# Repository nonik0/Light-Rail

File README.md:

# Light Rail

## Overview & Acknowledgements

Light Rail is a minimalist, interactive PCB game that simulates trains traveling along tracks, picking up and delivering cargo from platforms. The track is composed of yellow LEDs arranged in lines, which illuminate sequentially to create the effect of trains moving along the tracks. Next to each of the eight forks and crosses in the track is a button to switch its state. The board also has a three-character seven-segment display for showing the game status and/or score and four more buttons underneath the track for gameplay control. Light Rail can be powered with two LIR2032 batteries or via USB.

I also want to acknowledge and thank [PCBWay](https://www.pcbway.com/) for their generous support of this project! Even before I had the initial idea, PCBWay had already reached out to me asking if I would like to collaborate on my next project. However, I didn't actually see the email until I started looking into how I wanted to manufacture prototypes for Light Rail. Just getting the email and seeing that others were liking my older projects gave me a big motivation boost to continue with this project, be creative, and make something of my own. Overall, my experience with PCBWay was great and I would definitely recommend checking them out for your own projects!

For more details about my design goals, process, and ordering and production experience with PCBWay, please see my full [project writeup](https://altonimb.us/light-rail/)!

### Work Left
- first working game prototype
- further game ideas and testing
- investigate CR2032 batteries in series

## Hardware
The hardware is designed in KiCad 8.0 and all design files are included in the [hardware/kicad8.0](hardware/kicad8.0) directory.

The main hardware components are:
- [ATMega32u4](https://www.microchip.com/en-us/product/atmega32u4) 8-bit MCU
- [IS31FL3731](https://www.lumissil.com/applications/industrial/appliance/major-appliances/range-hood/is31fl3731) matrix LED driver (charliplexing)
- [AS1115](https://ams-osram.com/products/drivers/led-drivers/ams-as1115-led-driver-ic) seven-segment LED display driver
- [KCSC02-105](https://www.kingbright.com/attachments/file/psearch/000/00/00/KCSC02-105(Ver.12A).pdf) seven-segment LED display
- [MIC5219](https://ww1.microchip.com/downloads/en/DeviceDoc/MIC5219-500mA-Peak-Output-LDO-Regulator-DS20006021A.pdf) 3.3V LDS Regulator
- Yellow "track" and red "platform" LEDs, 144 total

See the [Bill of Material (BoM)](hardware/documents/Light_Rail_BOM.xlsx) for complete list of components used and my [project writeup](WRITEUP.md) for more details.

## Firmware

The firmware initially started as a C++/PlatformIO project, which can be found in the [firmware/cpp](firmware/cpp) directory. Before I actually received the inital prototype boards I decided to pivot and write everything in Rust, which can be found in the [firmware/rust](firmware/rust) directory. As part of the effort to get back to where I left off with the C++ firmware, I did the following:
- Wrote a new [AS1115 driver](https://github.com/nonik0/as1115)
- Wrote new tone library for avr-hal (TODO: integrate into avr-hal and open PR)
- Updated existing fork of [IS31FL3731](https://github.com/nonik0/is31fl3731) driver to latest embedded-hal with other minor additions

TODO: basic overview of game design and firmware components (in second writeup?)

## Images

#### Prototype

#### Schematic

#### PCB Layout

#### Render

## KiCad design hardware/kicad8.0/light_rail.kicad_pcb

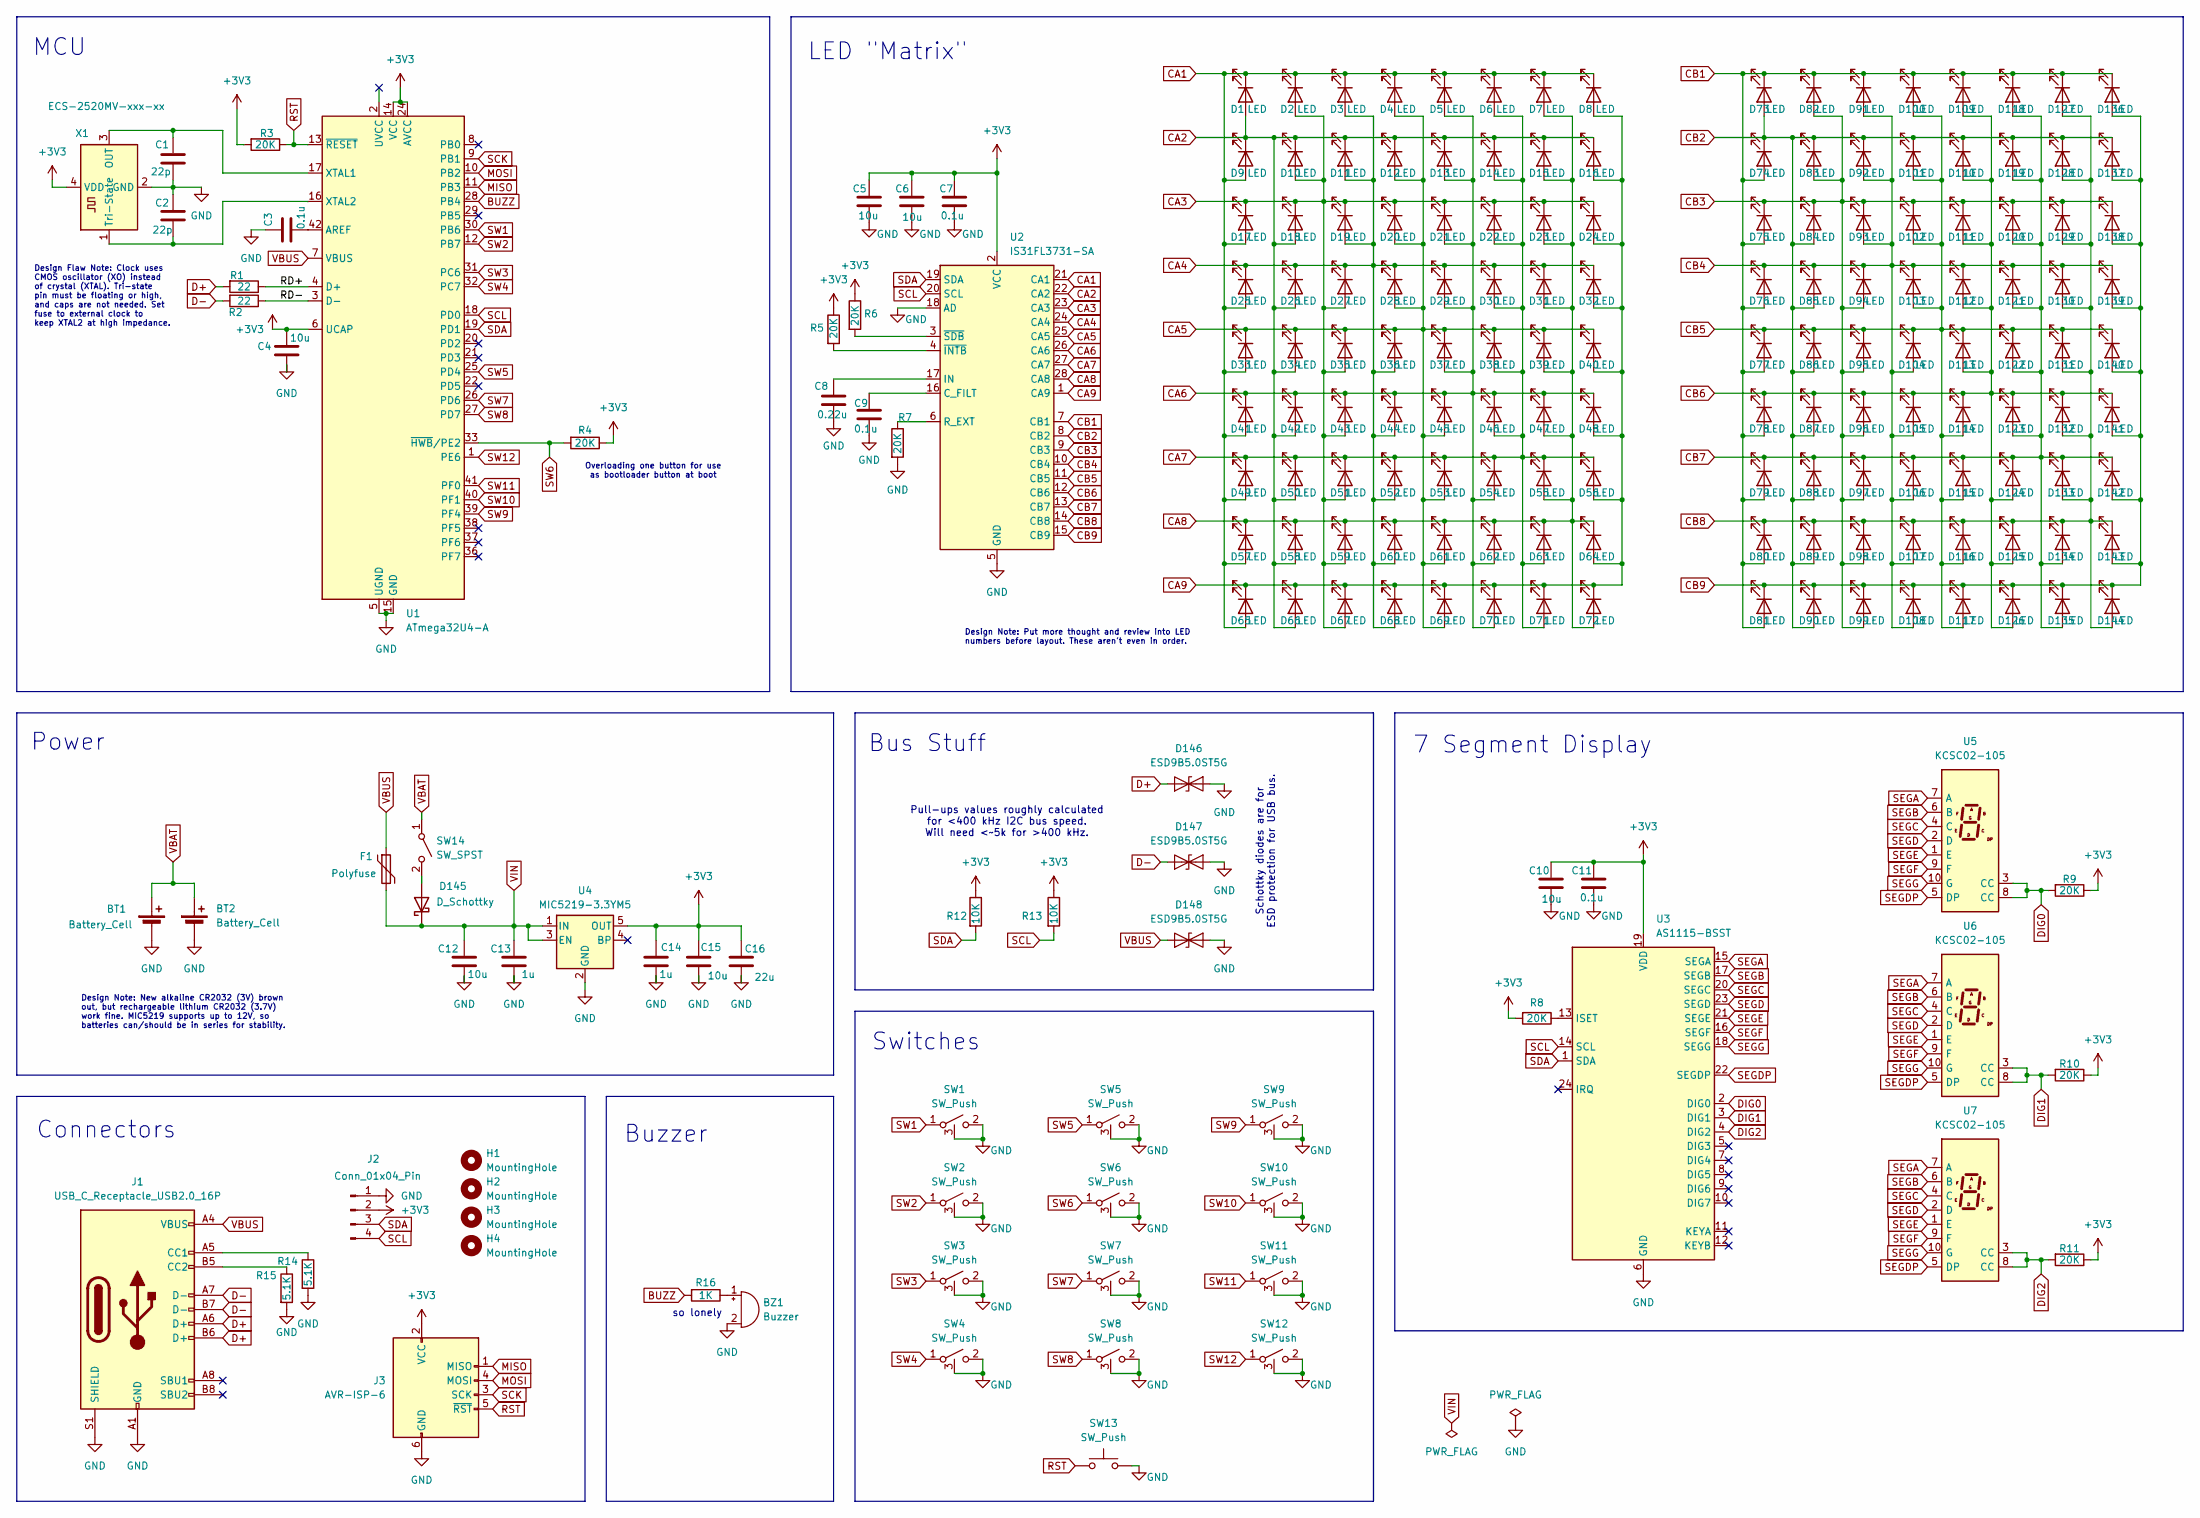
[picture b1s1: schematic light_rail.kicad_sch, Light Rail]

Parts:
BT1, BT2: Battery_Cell; BatteryHolder_Keystone_3034_1x20mm
BZ1: Buzzer; Buzzer_Murata_PKLCS1212E
C1, C2: 22p; C_0805_2012Metric
C3, C7, C9, C11: 0.1u; C_0805_2012Metric
C4, C5, C6, C10, C12, C15: 10u; C_0805_2012Metric
C8: 0.22u; C_0805_2012Metric
C13, C14: 1u; C_0805_2012Metric
C16: 22u; C_0805_2012Metric
D1, D9, D10, D16, D17, D18, D19, D21, D23, D27, D28, D32, D39, D41, D43, D48, D49, D50, D53, D54, D57, D59, D60, D61, D63, D64, D66, D68, D69, D70, D76, D85, D86, D88, D96, D97, D100, D101, D103, D105, D106, D108, D114, D117, D118, D121, D122, D123, D124, D125, D128, D132, D135, D137, D139, D140, D141, D143: LED; LED_0805_TrainTrack
D2, D6, D7, D12, D14, D20, D26, D33, D34, D36, D47, D58, D62, D71, D75, D78, D89, D92, D94, D104, D110, D111, D112, D115, D116, D134, D136: LED; LED_0805_NoSilkscreen
D3, D11, D38, D46, D67: LED; LED_0805_TrainTrackBendStart3
D4, D35, D72, D90, D91, D99, D102, D109, D127, D142: LED; LED_0805_TrainTrackBendStart4
D5, D13, D15, D22, D25, D37, D42, D44, D45, D79, D82, D83, D84, D120, D133, D138, D144: LED; LED_0805_TrainTrackBend1
D8, D30, D52, D56, D65, D74, D77, D98, D129, D130: LED; LED_0805_TrainTrackBend2
D24, D40, D51, D55, D73, D93, D126, D131: LED; LED_0805_TrainTrackEmpty
D29: LED; LED_0805_TrainTrackInnerBend2
D31, D80, D87: LED; LED_0805_TrainTrackBendStart2
D81, D95, D107, D119: LED; LED_0805_TrainTrackBendStart1
D113: LED; LED_0805_TrainTrackInnerBend1
D145: D_Schottky; D_0805_2012Metric
D146, D147, D148: ESD9B5.0ST5G; D_0402_1005Metric
F1: Polyfuse; D_0603_1608Metric
H1, H2, H3, H4: MountingHole; MountingHole_Custom
J1: USB_C_Receptacle_USB2.0_16P; USB_C_Receptacle_HCTL_HC-TYPE-C-16P-01A
J2: Conn_01x04_Pin; PinHeader_1x04_P2.54mm_Vertical
J3: AVR-ISP-6; PinHeader_2x03_P2.54mm_Vertical
R1, R2: 22; R_0805_2012Metric
R3, R4, R5, R6, R7, R8, R9, R10, R11: 20K; R_0805_2012Metric
R12, R13: 10K; R_0805_2012Metric
R14, R15: 5.1K; R_0603_1608Metric
R16: 1K; R_0805_2012Metric
SW1, SW2, SW3, SW4, SW5, SW6, SW7, SW8, SW9, SW10, SW11, SW12: SW_Push; SW_SPST_PTS526_JLeadsWGndPin
SW13: SW_Push; SW_Push_SPST_NO_Alps_SKRK
SW14: SW_SPST; SW_SPDT_PCM12
U1: ATmega32U4-A; TQFP-44_10x10mm_P0.8mm
U2: IS31FL3731-SA; SSOP-28_5.3x10.2mm_P0.65mm
U3: AS1115-BSST; QSOP-24_3.9x8.7mm_P0.635mm
U4: MIC5219-3.3YM5; SOT-23-5
U5, U6, U7: KCSC02-105
X1: ECS-2520MV-xxx-xx; Oscillator_SMD_ECS_2520MV-xxx-xx-4Pin_2.5x2.0mm

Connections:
+3V3: C4.1, C5.1, C6.1, C7.1, C10.1, C11.1, C14.1, C15.1, C16.1, J2.2, J3.2 (VCC), R3.2, R4.1, R5.1, R6.1, R8.2, R9.1, R10.1, R11.1, R12.1, R13.1, U1.6 (UCAP), U1.14 (VCC), U1.24 (AVCC), U1.34 (VCC), U1.44 (AVCC), U2.2 (VCC), U3.19 (VDD), U4.5 (OUT), X1.4 (VDD)
/RD+: R1.1, U1.4 (D+)
/RD-: R2.1, U1.3 (D-)
BUZZ: R16.2, U1.28 (PB4)
CA1: D1.1 (K), D2.1 (K), D3.1 (K), D4.1 (K), D5.1 (K), D6.1 (K), D7.1 (K), D8.1 (K), D9.2 (A), D17.2 (A), D25.2 (A), D33.2 (A), D41.2 (A), D49.2 (A), D57.2 (A), D65.2 (A), U2.21 (CA1)
CA2: D1.2 (A), D9.1 (K), D10.1 (K), D11.1 (K), D12.1 (K), D13.1 (K), D14.1 (K), D15.1 (K), D16.1 (K), D18.2 (A), D26.2 (A), D34.2 (A), D42.2 (A), D50.2 (A), D58.2 (A), D66.2 (A), U2.22 (CA2)
CA3: D2.2 (A), D10.2 (A), D17.1 (K), D18.1 (K), D19.1 (K), D20.1 (K), D21.1 (K), D22.1 (K), D23.1 (K), D24.1 (K), D27.2 (A), D35.2 (A), D43.2 (A), D51.2 (A), D59.2 (A), D67.2 (A), U2.23 (CA3)
CA4: D3.2 (A), D11.2 (A), D19.2 (A), D25.1 (K), D26.1 (K), D27.1 (K), D28.1 (K), D29.1 (K), D30.1 (K), D31.1 (K), D32.1 (K), D36.2 (A), D44.2 (A), D52.2 (A), D60.2 (A), D68.2 (A), U2.24 (CA4)
CA5: D4.2 (A), D12.2 (A), D20.2 (A), D28.2 (A), D33.1 (K), D34.1 (K), D35.1 (K), D36.1 (K), D37.1 (K), D38.1 (K), D39.1 (K), D40.1 (K), D45.2 (A), D53.2 (A), D61.2 (A), D69.2 (A), U2.25 (CA5)
CA6: D5.2 (A), D13.2 (A), D21.2 (A), D29.2 (A), D37.2 (A), D41.1 (K), D42.1 (K), D43.1 (K), D44.1 (K), D45.1 (K), D46.1 (K), D47.1 (K), D48.1 (K), D54.2 (A), D62.2 (A), D70.2 (A), U2.26 (CA6)
CA7: D6.2 (A), D14.2 (A), D22.2 (A), D30.2 (A), D38.2 (A), D46.2 (A), D49.1 (K), D50.1 (K), D51.1 (K), D52.1 (K), D53.1 (K), D54.1 (K), D55.1 (K), D56.1 (K), D63.2 (A), D71.2 (A), U2.27 (CA7)
CA8: D7.2 (A), D15.2 (A), D23.2 (A), D31.2 (A), D39.2 (A), D47.2 (A), D55.2 (A), D57.1 (K), D58.1 (K), D59.1 (K), D60.1 (K), D61.1 (K), D62.1 (K), D63.1 (K), D64.1 (K), D72.2 (A), U2.28 (CA8)
CA9: D8.2 (A), D16.2 (A), D24.2 (A), D32.2 (A), D40.2 (A), D48.2 (A), D56.2 (A), D64.2 (A), D65.1 (K), D66.1 (K), D67.1 (K), D68.1 (K), D69.1 (K), D70.1 (K), D71.1 (K), D72.1 (K), U2.1 (CA9)
CB1: D73.1 (K), D74.2 (A), D75.2 (A), D76.2 (A), D77.2 (A), D78.2 (A), D79.2 (A), D80.2 (A), D81.2 (A), D82.1 (K), D91.1 (K), D100.1 (K), D109.1 (K), D118.1 (K), D127.1 (K), D136.1 (K), U2.7 (CB1)
CB2: D73.2 (A), D74.1 (K), D83.1 (K), D84.2 (A), D85.2 (A), D86.2 (A), D87.2 (A), D88.2 (A), D89.2 (A), D90.2 (A), D92.1 (K), D101.1 (K), D110.1 (K), D119.1 (K), D128.1 (K), D137.1 (K), U2.8 (CB2)
CB3: D75.1 (K), D82.2 (A), D83.2 (A), D84.1 (K), D93.1 (K), D94.2 (A), D95.2 (A), D96.2 (A), D97.2 (A), D98.2 (A), D99.2 (A), D102.1 (K), D111.1 (K), D120.1 (K), D129.1 (K), D138.1 (K), U2.9 (CB3)
CB4: D76.1 (K), D85.1 (K), D91.2 (A), D92.2 (A), D93.2 (A), D94.1 (K), D103.1 (K), D104.2 (A), D105.2 (A), D106.2 (A), D107.2 (A), D108.2 (A), D112.1 (K), D121.1 (K), D130.1 (K), D139.1 (K), U2.10 (CB4)
CB5: D77.1 (K), D86.1 (K), D95.1 (K), D100.2 (A), D101.2 (A), D102.2 (A), D103.2 (A), D104.1 (K), D113.1 (K), D114.2 (A), D115.2 (A), D116.2 (A), D117.2 (A), D122.1 (K), D131.1 (K), D140.1 (K), U2.11 (CB5)
CB6: D78.1 (K), D87.1 (K), D96.1 (K), D105.1 (K), D109.2 (A), D110.2 (A), D111.2 (A), D112.2 (A), D113.2 (A), D114.1 (K), D123.1 (K), D124.2 (A), D125.2 (A), D126.2 (A), D132.1 (K), D141.1 (K), U2.12 (CB6)
CB7: D79.1 (K), D88.1 (K), D97.1 (K), D106.1 (K), D115.1 (K), D118.2 (A), D119.2 (A), D120.2 (A), D121.2 (A), D122.2 (A), D123.2 (A), D124.1 (K), D133.1 (K), D134.2 (A), D135.2 (A), D142.1 (K), U2.13 (CB7)
CB8: D80.1 (K), D89.1 (K), D98.1 (K), D107.1 (K), D116.1 (K), D125.1 (K), D127.2 (A), D128.2 (A), D129.2 (A), D130.2 (A), D131.2 (A), D132.2 (A), D133.2 (A), D134.1 (K), D143.1 (K), D144.2 (A), U2.14 (CB8)
CB9: D81.1 (K), D90.1 (K), D99.1 (K), D108.1 (K), D117.1 (K), D126.1 (K), D135.1 (K), D136.2 (A), D137.2 (A), D138.2 (A), D139.2 (A), D140.2 (A), D141.2 (A), D142.2 (A), D143.2 (A), D144.1 (K), U2.15 (CB9)
D+: D146.1 (A1), J1.A6 (D+), J1.B6 (D+), R1.2
D-: D147.1 (A1), J1.A7 (D-), J1.B7 (D-), R2.2
DIG0: R9.2, U3.2 (DIG0), U5.3 (CC), U5.8 (CC)
DIG1: R10.2, U3.3 (DIG1), U6.3 (CC), U6.8 (CC)
DIG2: R11.2, U3.4 (DIG2), U7.3 (CC), U7.8 (CC)
GND: BT1.2 (-), BT2.2 (-), BZ1.2 (-), C1.2, C2.1, C3.1, C4.2, C5.2, C6.2, C7.2, C8.2, C9.2, C10.2, C11.2, C12.2, C13.2, C14.2, C15.2, C16.2, D146.2 (A2), D147.2 (A2), D148.2 (A2), J1.A1 (GND), J1.A12 (GND), J1.B1 (GND), J1.B12 (GND), J1.S1 (SHIELD), J2.1, J3.6 (GND), R7.2, R14.2, R15.2, SW1.2 (B), SW1.3 (GND), SW2.2 (B), SW2.3 (GND), SW3.2 (B), SW3.3 (GND), SW4.2 (B), SW4.3 (GND), SW5.2 (B), SW5.3 (GND), SW6.2 (B), SW6.3 (GND), SW7.2 (B), SW7.3 (GND), SW8.2 (B), SW8.3 (GND), SW9.2 (B), SW9.3 (GND), SW10.2 (B), SW10.3 (GND), SW11.2 (B), SW11.3 (GND), SW12.2 (B), SW12.3 (GND), SW13.2, U1.5 (UGND), U1.15 (GND), U1.23 (GND), U1.35 (GND), U1.43 (GND), U2.5 (GND), U2.18 (AD), U3.6 (GND), U4.2 (GND), X1.2 (GND)
MISO: J3.1 (MISO), U1.11 (PB3)
MOSI: J3.4 (MOSI), U1.10 (PB2)
unnamed: BZ1.1 (+), R16.1
unnamed: D145.2 (A), SW14.2 (B)
unnamed: J1.A5 (CC1), R14.1
unnamed: J1.B5 (CC2), R15.1
unnamed: C3.2, U1.42 (AREF)
unnamed: C1.1, U1.17 (XTAL1), X1.3 (OUT)
unnamed: C2.2, U1.16 (XTAL2), X1.1 (Tri-State)
unnamed: C9.1, U2.16 (C_FILT)
unnamed: C8.1, U2.17 (IN)
unnamed: R7.1, U2.6 (R_EXT)
unnamed: R5.2, U2.4 (~INTB)
unnamed: R6.2, U2.3 (~SDB)
unnamed: R8.1, U3.13 (ISET)
RST: J3.5 (~RST), R3.1, SW13.1, U1.13 (~RESET)
SCK: J3.3 (SCK), U1.9 (PB1)
SCL: J2.4, R13.2, U1.18 (PD0), U2.20 (SCL), U3.14 (SCL)
SDA: J2.3, R12.2, U1.19 (PD1), U2.19 (SDA), U3.1 (SDA)
SEGA: U3.15 (SEGA), U5.7 (A), U6.7 (A), U7.7 (A)
SEGB: U3.17 (SEGB), U5.6 (B), U6.6 (B), U7.6 (B)
SEGC: U3.20 (SEGC), U5.4 (C), U6.4 (C), U7.4 (C)
SEGD: U3.23 (SEGD), U5.2 (D), U6.2 (D), U7.2 (D)
SEGDP: U3.22 (SEGDP), U5.5 (DP), U6.5 (DP), U7.5 (DP)
SEGE: U3.21 (SEGE), U5.1 (E), U6.1 (E), U7.1 (E)
SEGF: U3.16 (SEGF), U5.9 (F), U6.9 (F), U7.9 (F)
SEGG: U3.18 (SEGG), U5.10 (G), U6.10 (G), U7.10 (G)
SW1: SW1.1 (A), U1.30 (PB6)
SW2: SW2.1 (A), U1.12 (PB7)
SW3: SW3.1 (A), U1.31 (PC6)
SW4: SW4.1 (A), U1.32 (PC7)
SW5: SW5.1 (A), U1.25 (PD4)
SW6: R4.2, SW6.1 (A), U1.33 (~HWB/PE2)
SW7: SW7.1 (A), U1.26 (PD6)
SW8: SW8.1 (A), U1.27 (PD7)
SW9: SW9.1 (A), U1.39 (PF4)
SW10: SW10.1 (A), U1.40 (PF1)
SW11: SW11.1 (A), U1.41 (PF0)
SW12: SW12.1 (A), U1.1 (PE6)
VBAT: BT1.1 (+), BT2.1 (+), SW14.1 (A)
VBUS: D148.1 (A1), F1.1, J1.A4 (VBUS), J1.A9 (VBUS), J1.B4 (VBUS), J1.B9 (VBUS), U1.7 (VBUS)
VIN: C12.1, C13.1, D145.1 (K), F1.2, U4.1 (IN), U4.3 (EN)

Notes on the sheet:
Design Flaw Note: Clock uses CMOS oscillator (XO) instead of crystal (XTAL). Tri-state pin must be floating or high, and caps are not needed. Set fuse to external clock to keep XTAL2 at high impedance.
Design Note: New alkaline CR2032 (3V) brown out, but rechargeable lithium CR2032 (3.7V) work fine. MIC5219 supports up to 12V, so batteries can/should be in series for stability.
Pull-ups values roughly calculated for <400 kHz I2C bus speed. Will need <~5k for >400 kHz.
LED "Matrix"
Design Note: Put more thought and review into LED numbers before layout. These aren't even in order.
Bus Stuff
Power
MCU
Buzzer
Connectors
Switches
so lonely
Overloading one button for use as bootloader button at boot
7 Segment Display
Schottky diodes are for ESD protection for USB bus.

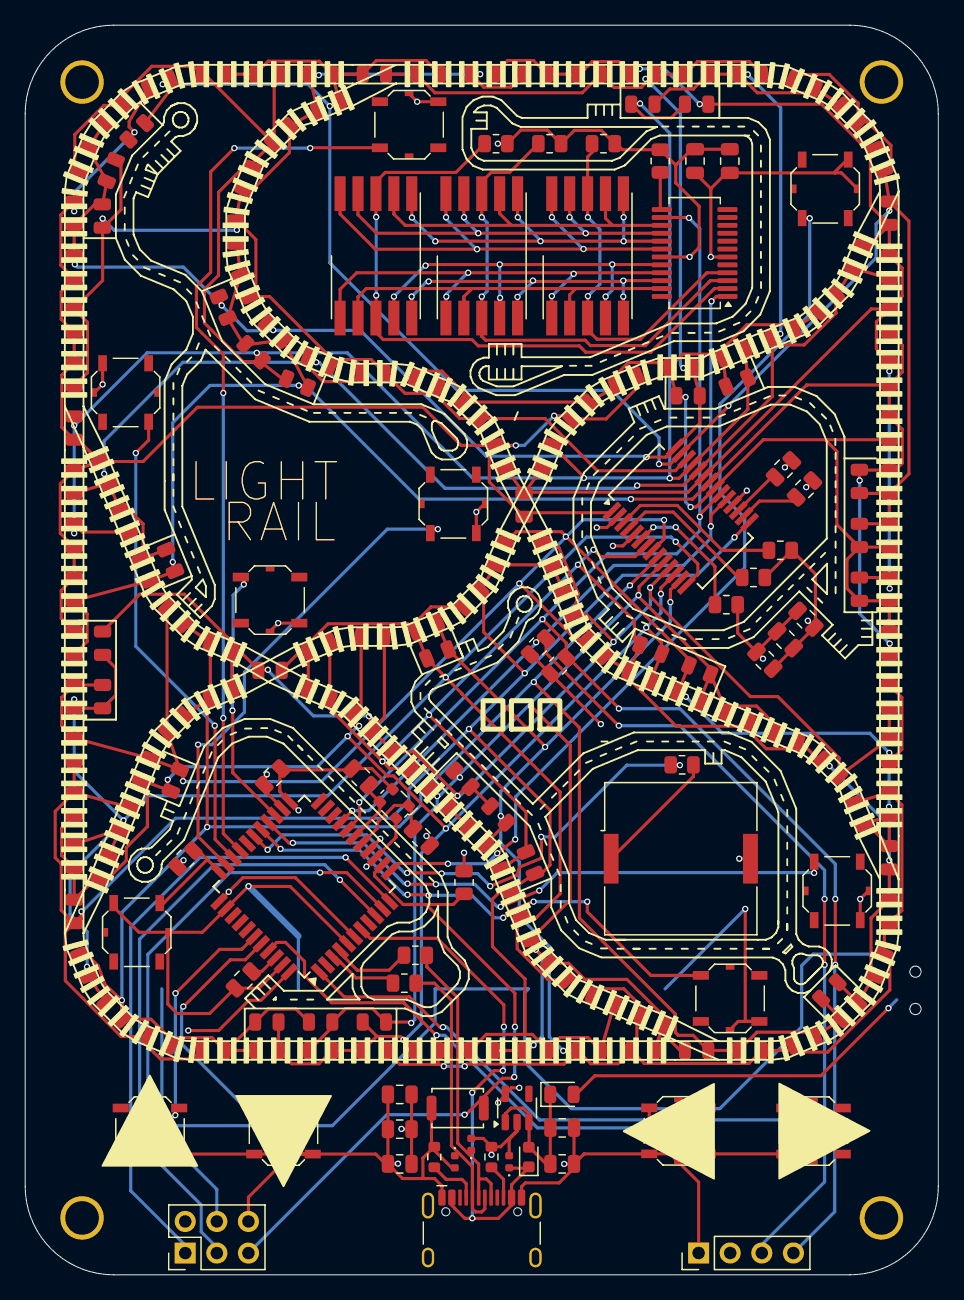
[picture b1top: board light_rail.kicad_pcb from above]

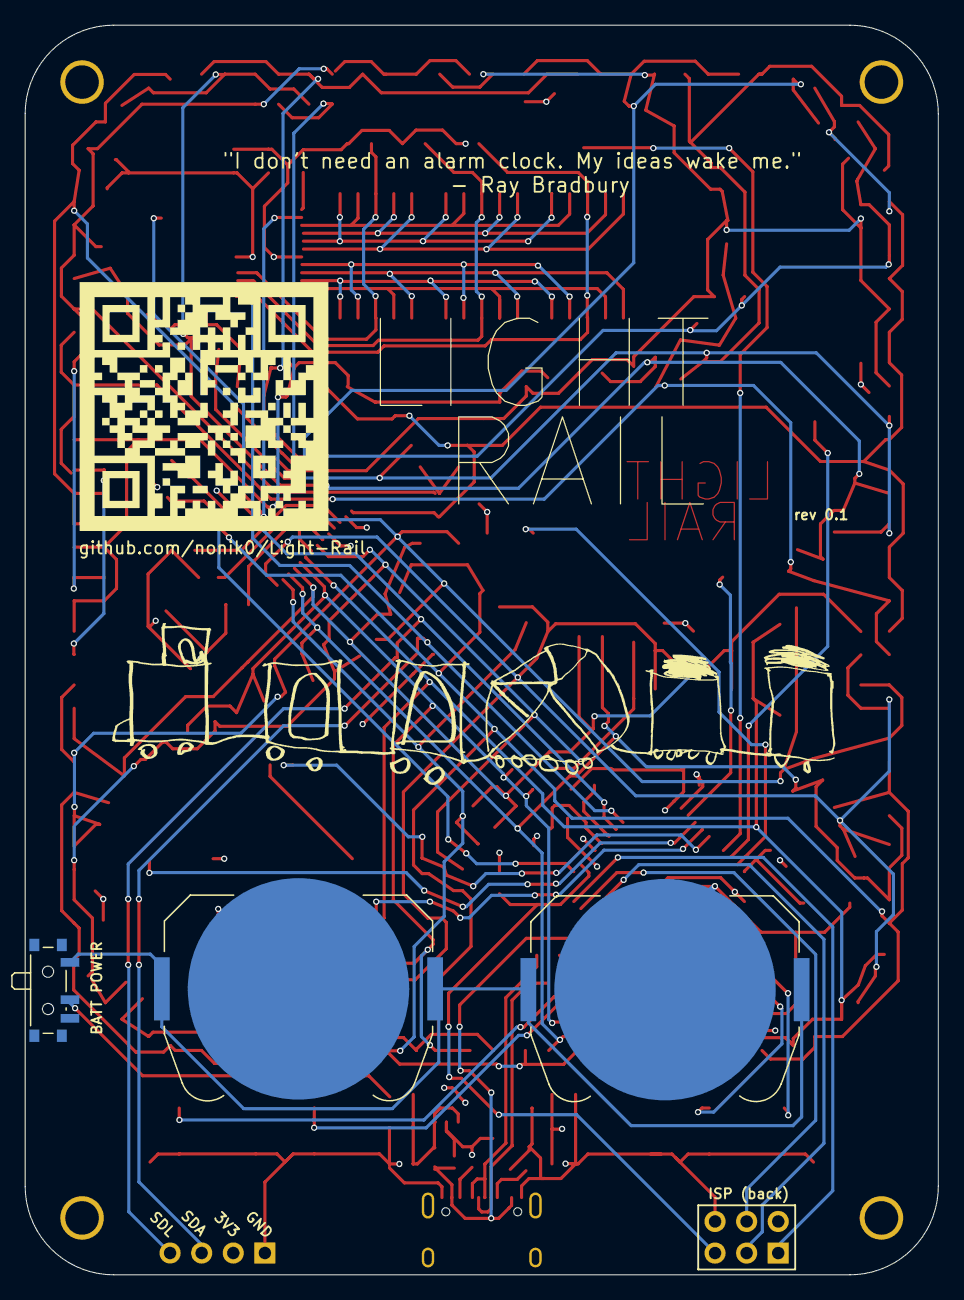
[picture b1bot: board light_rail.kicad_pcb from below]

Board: 4 copper layers, 73.4 x 100.5 mm, 213 parts (3 on the bottom side), 70 nets.

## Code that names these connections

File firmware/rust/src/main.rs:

#![no_std]
#![no_main]
#![feature(abi_avr_interrupt)]
#![feature(const_trait_impl)]
#![feature(panic_info_message)]
#![feature(type_alias_impl_trait)]

// TODO: can print to digits before panic halting
#[cfg(not(feature = "panic_to_digits"))]
#[macro_export]
macro_rules! panic_with_error {
    ($error_code:expr) => {
        panic!()
    };
}

use atmega_hal::adc;
use core::cell::RefCell;
use embedded_hal::delay::DelayNs;
use embedded_hal_bus::i2c::{self};
#[cfg(not(feature = "panic_to_digits"))]
use panic_halt as _;

type Adc = atmega_hal::adc::Adc<CoreClock>;
#[cfg(feature = "atmega32u4")]
type CoreClock = atmega_hal::clock::MHz8;
#[cfg(feature = "atmega328p")]
type CoreClock = atmega_hal::clock::MHz16;
type Delay = atmega_hal::delay::Delay<CoreClock>;
type Eeprom = atmega_hal::eeprom::Eeprom;
type I2c = atmega_hal::i2c::I2c<CoreClock>;

mod cargo;
mod game;
mod game_settings;
mod game_state;
mod input;
mod location;
mod modes;
#[cfg(feature = "panic_to_digits")]
mod panic;
mod platform;
mod random;
mod switch;
#[cfg_attr(not(feature = "atmega32u4"), path = "notone.rs")]
mod tone;
mod train;

const NUM_BUTTONS: usize = 12;
const NUM_DIGITS: u8 = 3;
const DIGITS_I2C_ADDR: u8 = as1115::DEFAULT_ADDRESS;
const LEDS_I2C_ADDR: u8 = is31fl3731::DEFAULT_ADDRESS;

#[avr_device::entry]
fn main() -> ! {
    let dp = atmega_hal::Peripherals::take().unwrap();
    let pins = atmega_hal::pins!(dp);
    let mut delay = Delay::new();
    let i2c = I2c::new(
        dp.TWI,
        #[cfg(feature = "atmega32u4")]
        pins.pd1.into_pull_up_input(),
        #[cfg(feature = "atmega328p")]
        pins.pc4.into_pull_up_input(),
        #[cfg(feature = "atmega32u4")]
        pins.pd0.into_pull_up_input(),
        #[cfg(feature = "atmega328p")]
        pins.pc5.into_pull_up_input(),
        400_000,
    );
    let i2c_ref_cell = RefCell::new(i2c);

    #[cfg(feature = "atmega32u4")]
    let board_buzzer = tone::TimerTone::new(dp.TC3, pins.pb4.into_output().downgrade());
    #[cfg(feature = "atmega328p")]
    let board_buzzer = tone::TimerTone::new();

    let eeprom = Eeprom::new(dp.EEPROM);
    let settings = game_settings::GameSettings::new(eeprom);

    let mut board_digits =
        as1115::AS1115::new_with_addr(i2c::RefCellDevice::new(&i2c_ref_cell), DIGITS_I2C_ADDR);
    board_digits.init(settings.digit_brightness_level()).ok();
    board_digits.clear().ok();

    #[cfg(feature = "atmega32u4")]
    let input_pins = [
        pins.pb6.into_pull_up_input().downgrade(),
        pins.pb7.into_pull_up_input().downgrade(),
        pins.pc6.into_pull_up_input().downgrade(),
        pins.pc7.into_pull_up_input().downgrade(),
        pins.pd4.into_pull_up_input().downgrade(),
        pins.pe2.into_pull_up_input().downgrade(),
        pins.pd6.into_pull_up_input().downgrade(),
        pins.pd7.into_pull_up_input().downgrade(),
        pins.pf4.into_pull_up_input().downgrade(),
        pins.pf1.into_pull_up_input().downgrade(),
        pins.pf0.into_pull_up_input().downgrade(),
        pins.pe6.into_pull_up_input().downgrade(),
    ];
    #[cfg(feature = "atmega328p")]
    let input_pins = [
        pins.pd0.into_pull_up_input().downgrade(),
        pins.pd1.into_pull_up_input().downgrade(),
        pins.pd2.into_pull_up_input().downgrade(),
        pins.pd3.into_pull_up_input().downgrade(),
        pins.pd4.into_pull_up_input().downgrade(),
        pins.pd5.into_pull_up_input().downgrade(),
        pins.pd6.into_pull_up_input().downgrade(),
        pins.pd7.into_pull_up_input().downgrade(),
        pins.pb0.into_pull_up_input().downgrade(),
        pins.pb1.into_pull_up_input().downgrade(),
        pins.pb2.into_pull_up_input().downgrade(),
        pins.pb3.into_pull_up_input().downgrade(),
    ];
    let board_input = input::BoardInput::new(input_pins);

    let mut board_leds =
        is31fl3731::IS31FL3731::new(i2c::RefCellDevice::new(&i2c_ref_cell), LEDS_I2C_ADDR);
    board_leds.setup_blocking(&mut delay).unwrap(); // TODO: why does OK hang???
    board_leds.clear_blocking().ok();

    // generate random seed from ADC temperature sensor
    let mut adc = Adc::new(dp.ADC, Default::default());
    let mut seed: u32 = 0;
    for i in 0..8 {
        // using 4 LSB bits x 8 readings for 32 bit seed
        let reading = adc.read_blocking(&adc::channel::Temperature);
        let lsb = (reading & 0xF) as u32;
        seed |= lsb << (i * 4);
    }
    random::Rand::seed(seed);

    let cars = [train::Car::default(); game_state::MAX_CARS];
    let mut game = game::Game::new(
        board_buzzer,
        board_digits,
        board_input,
        board_leds,
        cars,
        settings,
    );
    game.restart();

    loop {
        game.tick();
        delay.delay_ms(game.base_delay());
    }
}

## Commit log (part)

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2024-11-15 changes for fab
2024-11-20 fab updates 2
2024-11-30 post-prod schematic fix, should be no change
2024-12-14 starting boilerplate
2024-12-14 more boilerplate work
2024-12-14 BoM fix
2024-12-15 basic working prototype
2024-12-15 minor stuff
2025-01-09 testing board
2025-01-09 rust firmware start
2025-01-09 partial progress
2025-01-09 untested full graph, switch tests
2025-01-09 working animation!
2025-01-09 BOM fix for RST switch
2025-01-14 fixes
2025-01-14 working is31 driver in rust
2025-01-15 as1115 driver
2025-01-15 use is31 github driver
2025-01-15 starting to figure out tone
2025-01-16 partial tone impl in rust
2025-01-16 some progress on timer
2025-01-17 rust progress
2025-01-19 minor
2025-01-28 working tone with timer1
2025-01-28 starting game structure
2025-01-29 location refactoring
2025-01-30 misc
2025-01-30 change to timer3
2025-01-31 game logic progress
2025-01-31 more progress, untested
2025-01-31 starting LocationUpdate changes
2025-02-01 location update impl
2025-02-02 progmem refactor in progress
2025-02-02 added design comments to schematic, added schematic image
2025-02-02 adding more images and moving around stuff
2025-02-02 resize images
2025-02-05 nearly there for basic animation demo
2025-02-05 first working train animation
2025-02-11 bug in graph data
2025-02-11 working train animation
2025-02-12 working platforms, with crappy rng
2025-02-12 score
2025-03-04 readme and images
2025-03-04 formatting readme
2025-04-02 writeup draft, minor
2025-04-10 adding images for writeup
2025-04-10 alt text and edits
2025-04-18 few more pics
2025-04-25 update writeup location
2025-05-08 static rng, input refactor untested
2025-05-12 no panics, rand issues still?
2025-05-13 adding atmega328p feature to help debug
2025-05-14 no debug-assertions == no rand panic
2025-05-14 input improvements
2025-05-14 tone back for 32u4 only
2025-05-15 input fix
2025-05-16 switch progress, try out panic error_code
2025-05-16 more switch progress
2025-05-18 switch indicator test
2025-05-18 working switches/crosses
2025-05-19 game mode structure
2025-05-19 defining game flow more
2025-05-20 game tick
2025-05-20 switch improvements
2025-05-20 some refactoring, freeplay boilerplate
2025-05-20 basic working modes
2025-05-21 remove entityupdate buffer, using closure instead
2025-05-21 removed static lifetimes
2025-05-21 location memory improvements
2025-05-21 restart callback
2025-05-24 minor tweaks
2025-06-02 rotate
2025-06-02 tweaks
2025-06-03 start of time mode
2025-06-03 refactoring entityupdates to ledupdates
2025-06-03 cleanup for restarts
2025-06-03 cargo changes
2025-06-04 basic patterns and pick up and drop off
2025-06-05 car refactor, dynamic train size tp save sram
2025-06-05 simple cars allocation
2025-06-05 freeplay testing
2025-06-05 misc improvements
2025-06-06 time gameplay
2025-06-08 game state to own file, panic feature
2025-06-08 code cleanup
2025-06-08 no more static modes, yay SRAM
2025-06-09 use enum_dispatch crate
2025-06-09 minor cleanup
2025-06-09 rename cargo
2025-06-13 settings mode
2025-06-13 eeprom for settings
2025-06-13 brightness settings adjustments
2025-06-13 buzzer setting
2025-06-14 segment animation
2025-06-14 path finding
2025-06-15 anim fixes, incomplete
2025-06-16 optimizations
2025-06-16 fixes, let snake get stuck for nwo
2025-06-16 rest of fixes for anim
2025-06-16 removing debug impl for lots of sram savings
2025-06-17 use decimals for timer indicator
2025-06-17 adjustments
2025-06-17 slow down patterns
2025-06-17 rand range, snake eats
2025-06-17 juggle mode, issue with modes
2025-06-18 juggle adj
2025-06-19 time improvements, pause, misc
2025-06-19 food spawn adj
2025-08-07 update as1115 dep
